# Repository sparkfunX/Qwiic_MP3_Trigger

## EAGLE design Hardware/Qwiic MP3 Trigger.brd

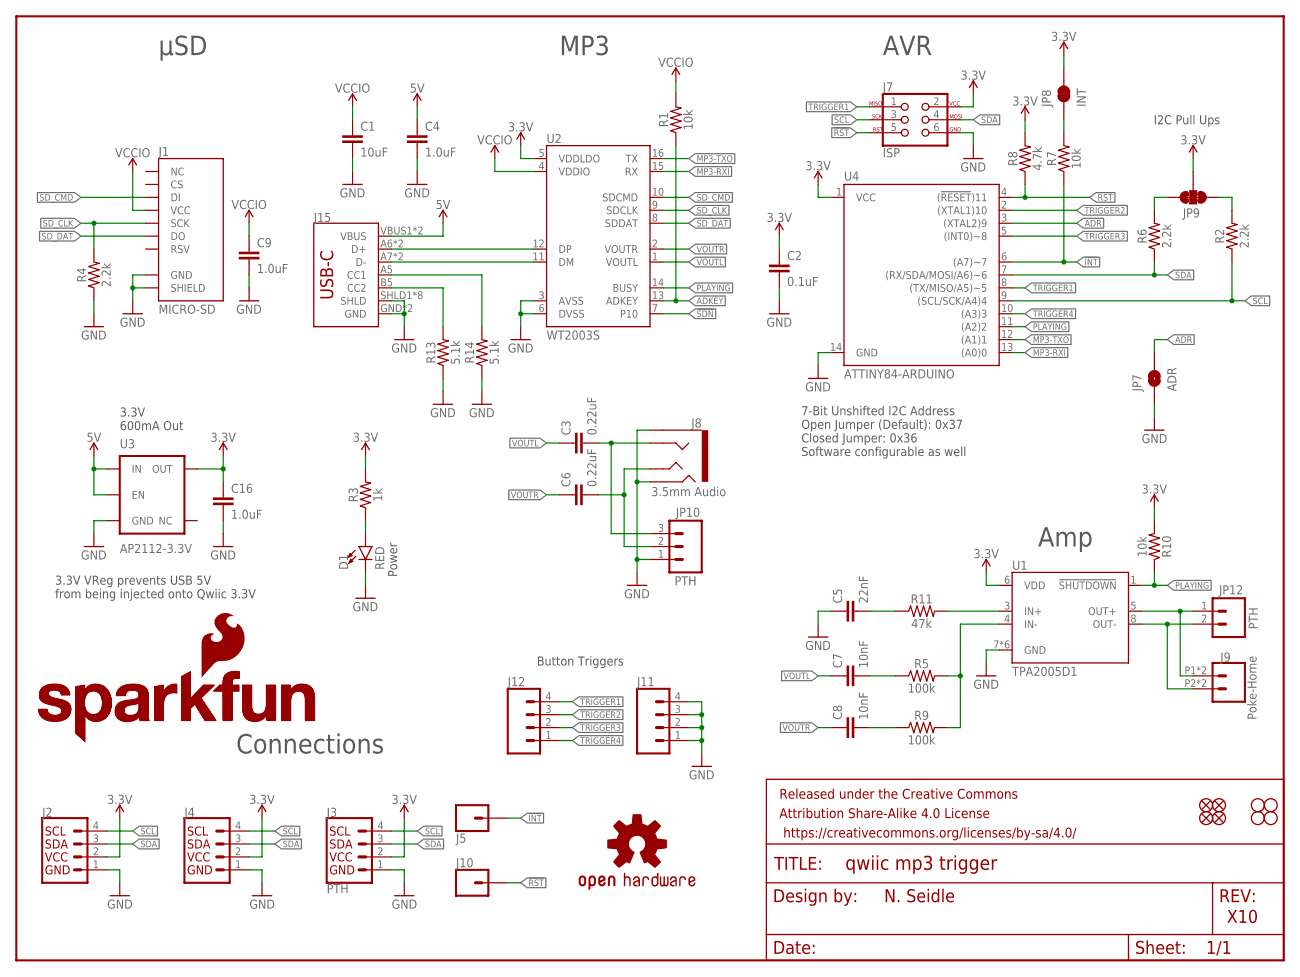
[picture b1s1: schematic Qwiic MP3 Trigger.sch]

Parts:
C1: 10uF; 0603
C2: 0.1uF; 0603
C3, C6: 0.22uF; 0603
C4, C9, C16: 1.0uF; 0603
C5: 22nF; 0603
C7, C8: 10nF; 0603
D1: RED; LED-0603
FRAME1: FRAME-LETTER; CREATIVE_COMMONS
J1: MICRO-SD; MICRO-SD-SOCKET
J2, J4: QWIIC_CONNECTORJS-1MM; 1X04_1MM_RA
J3: PTH; 1X04_NO_SILK
J5, J10: CONN_01PTH_NO_SILK_YES_STOP; 1X01_NO_SILK
J7: ISP; 2X3_TEST_POINTS
J8: 3.5mm Audio; AUDIO_JACK_3.5MM_TRRS_SMD_RA
J9: Poke-Home; 1X02_POKEHOME
J11, J12: CONN_041X04_NO_SILK; 1X04_NO_SILK
J15: USB_C16PIN; USB-C-16P
JP1, JP2, JP5, JP6: FIDUCIALUFIDUCIAL; MICRO-FIDUCIAL
JP3, JP4, JP11, JP13: STAND-OFF
JP7: ADR; SMT-JUMPER_2_NO_SILK
JP8: INT; SMT-JUMPER_2_NC_TRACE_SILK
JP9: JUMPER-SMT_3_2-NC_TRACE_SILK; SMT-JUMPER_3_2-NC_TRACE_SILK
JP10: PTH; 1X03_NO_SILK
JP12: PTH; 1X02_NO_SILK
LOGO1: OSHW-LOGOMINI; OSHW-LOGO-MINI
LOGO2: SFE_LOGO_NAME.1_INCH; SFE_LOGO_NAME_.1
LOGO3: SFE_LOGO_NAME_FLAME.1_INCH; SFE_LOGO_NAME_FLAME_.1
R1, R7, R10: 10k; 0603
R2, R4, R6: 2.2k; 0603
R3: 1k; 0603
R5, R9: 100k; 0603
R8: 4.7k; 0603
R11: 47k; 0603
R13, R14: 5.1k; 0603
U1: TPA2005D1; QFN-8_PAD
U2: WT2003S; SO16
U3: AP2112-3.3V; SOT23-5
U4: ATTINY84-ARDUINO; SO14

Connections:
3.3V: C2.1, C16.1, J2.2, J3.2 (VCC), J4.2, J7.2, JP8.2, JP9.2, R3.2, R8.2, R10.2, U1.6 (VDD), U2.5 (VDDLDO), U3.5 (OUT), U4.1 (VCC)
5V: C4.1, J15.VBUS1 (VBUS), J15.VBUS2 (VBUS), U3.1 (IN), U3.3 (EN)
!INT: J5.1, R7.1, U4.6 ((A7)~7)
!RST: J7.5, J10.1, R8.1, U4.4 ((!RESET!)11)
!SDN: U2.7 (P10)
AC-L: C3.2, J8.RING1, JP10.3
AC-R: C6.2, J8.TIP, JP10.2
ADKEY: R1.1, U2.13 (ADKEY)
ADR: JP7.2, U4.3 ((XTAL2)9)
D+: J15.A6 (D+), J15.B6 (D+), U2.12 (DP)
D-: J15.A7 (D-), J15.B7 (D-), U2.11 (DM)
GND: C1.2, C2.2, C4.2, C5.1, C9.2, C16.2, D1.C, J1.CD1 (SHIELD), J1.GND, J2.1, J3.1 (GND), J4.1, J7.6, J8.EARTH, J8.RING2, J11.1, J11.2, J11.3, J11.4, J15.GND, J15.GND2 (GND), J15.SHLD1 (SHLD), J15.SHLD2 (SHLD), J15.SHLD3 (SHLD), J15.SHLD4 (SHLD), J15.SHLD5 (SHLD), J15.SHLD6 (SHLD), J15.SHLD7 (SHLD), J15.SHLD8 (SHLD), JP7.1, JP10.1, R4.1, R13.1, R14.1, U1.7 (GND), U1.9 (GND), U1.10 (GND), U1.11 (GND), U1.12 (GND), U1.13 (GND), U2.3 (AVSS), U2.6 (DVSS), U3.2 (GND), U4.14 (GND)
IN+AMP: R11.2, U1.3 (IN+)
IN-AMP: R5.2, R9.2, U1.4 (IN-)
MP3-RXI: U2.15 (RX), U4.13 ((A0)0)
MP3-TXO: U2.16 (TX), U4.12 ((A1)1)
unnamed: J15.B5 (CC2), R13.2
unnamed: J15.A5 (CC1), R14.2
unnamed: D1.A, R3.1
unnamed: JP8.1, R7.2
unnamed: C8.2, R9.1
unnamed: C5.2, R11.1
unnamed: C7.2, R5.1
OUT+: J9.P1 (1), J9.P3 (1), JP12.1, U1.5 (OUT+)
OUT-: J9.P2 (2), J9.P4 (2), JP12.2, U1.8 (OUT-)
PLAYING: R10.1, U1.1 (!SHUTDOWN), U2.14 (BUSY), U4.11 ((A2)2)
SCL: J2.4, J3.4 (SCL), J4.4, J7.3, R2.1, U4.9 ((SCL/SCK/A4)4)
SCL_PU1: JP9.1, R2.2
SDA: J2.3, J3.3 (SDA), J4.3, J7.4, R6.1, U4.7 ((RX/SDA/MOSI/A6)~6)
SDA_PU1: JP9.3, R6.2
SD_CLK: J1.SCLK (SCK), R4.2, U2.9 (SDCLK)
SD_CMD: J1.DI, U2.10 (SDCMD)
SD_DAT: J1.DO, U2.8 (SDDAT)
TRIGGER1: J7.1, J12.4, U4.8 ((TX/MISO/A5)~5)
TRIGGER2: J12.3, U4.2 ((XTAL1)10)
TRIGGER3: J12.2, U4.5 ((INT0)~8)
TRIGGER4: J12.1, U4.10 ((A3)3)
VCCIO: C1.1, C9.1, J1.VCC, R1.2, U2.4 (VDDIO)
VOUTL: C3.1, C7.1, U2.1 (VOUTL)
VOUTR: C6.1, C8.1, U2.2 (VOUTR)

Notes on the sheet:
N. Seidle
X10
Power
7-Bit Unshifted I2C Address Open Jumper (Default): 0x37 Closed Jumper: 0x36 Software configurable as well
I2C Pull Ups
Button Triggers
3.3V VReg prevents USB 5V from being injected onto Qwiic 3.3V
3.3V 600mA Out
μSD
MP3
AVR
Amp
Connections

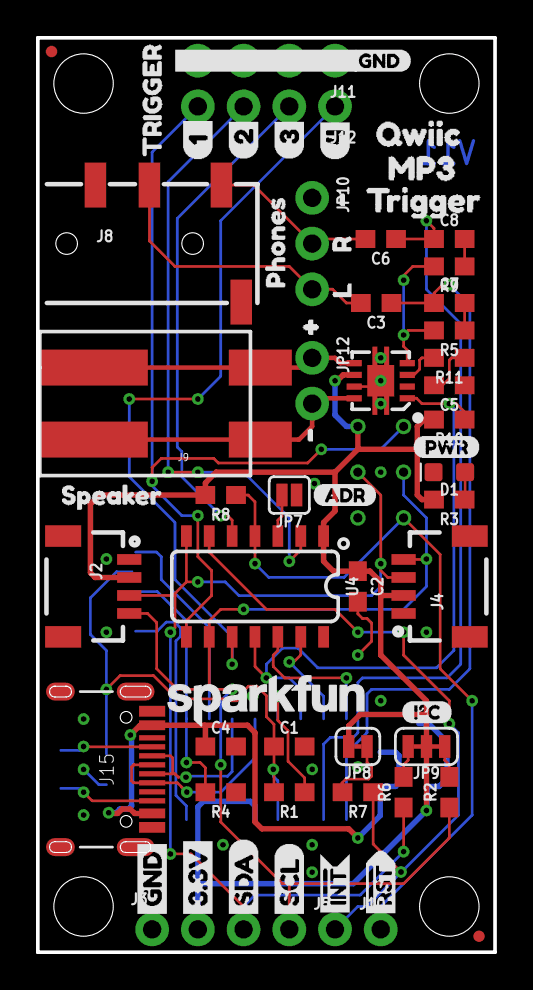
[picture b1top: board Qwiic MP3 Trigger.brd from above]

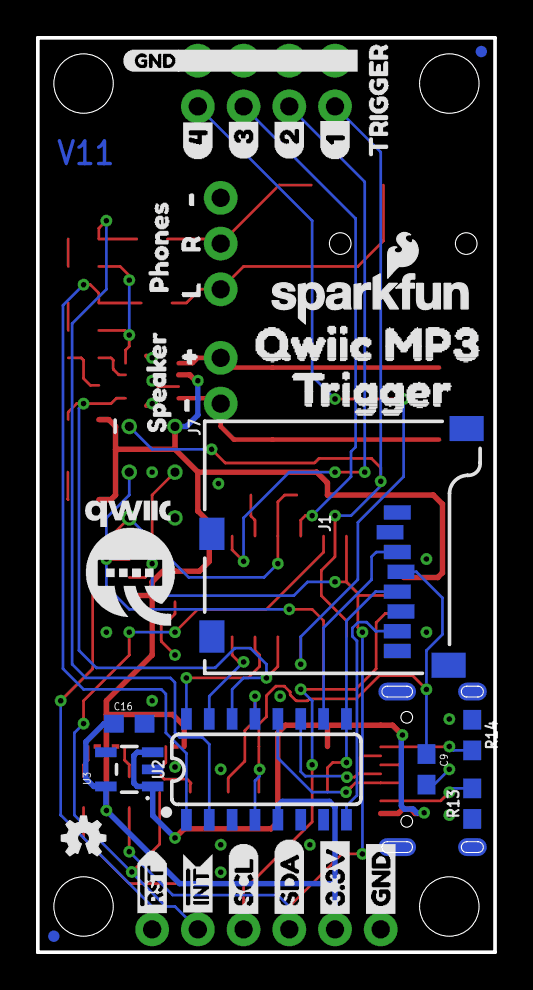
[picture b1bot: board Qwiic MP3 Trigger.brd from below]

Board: 2 copper layers, 25.4 x 50.8 mm, 104 parts (34 on the bottom side), 39 nets.

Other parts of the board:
U$1: MP31
U$3, U$22: GND1
U$4, U$21: 3#3V2
U$5, U$27: SDA8
U$6, U$26: SCL9
U$7, U$16: RST#-[>
U$8: I_SUPER2_C-()-03
U$9, U$11: INT#-[<
U$10, U$13, U$25, U$38: #6
U$12, U$28: #5
U$14, U$20: SPEAKER1
U$15, U$40: PHONES0
U$17: PWR-()-03
U$18: ADR-()-03
U$19, U$44: 1_1
U$23: QWIIC0
U$24: QWIIC_MP32
U$29, U$45: TRIGGER5
U$31, U$34: 43
U$32, U$42: 21
U$33, U$36: 32
U$35, U$46: GND0
U$37, U$41: L12
U$39, U$43: R11
U$47: QWIIC-LOGO-MEDIUM
U$49: TRIGGER4
U$50: TRIGGER2

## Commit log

2020-06-30 Modify RCs on amp input to match impedance. Should reduce pop and gain a bit.
2020-06-30 Increment version number on sch

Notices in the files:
parts and their libraries:
SparkFun-Resistors: Licensing: Creative Commons ShareAlike 4.0 International - https://creativecommons.org/licenses/by-sa/4.0
SparkFun-Aesthetics: Released under the Creative Commons Attribution Share-Alike 4.0 License
SparkFun-Aesthetics: https://creativecommons.org/licenses/by-sa/4.0
